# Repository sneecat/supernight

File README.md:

# Supernight
Supernight is a series of wifi LED controllers with the following features:

- High current capability (8A per-channel)
- 10 bit dimming
- 25kHz+ PWM for flicker-free film operation
- Lo-Mode 1kHz PWM for higher contrast ratio
- Physical controls
- Manual override
- ArtNet compatible (lumenair, etc.)

This is a work in progress. Currently I am going into software development, to ensure that my PCB is sound before ordering.

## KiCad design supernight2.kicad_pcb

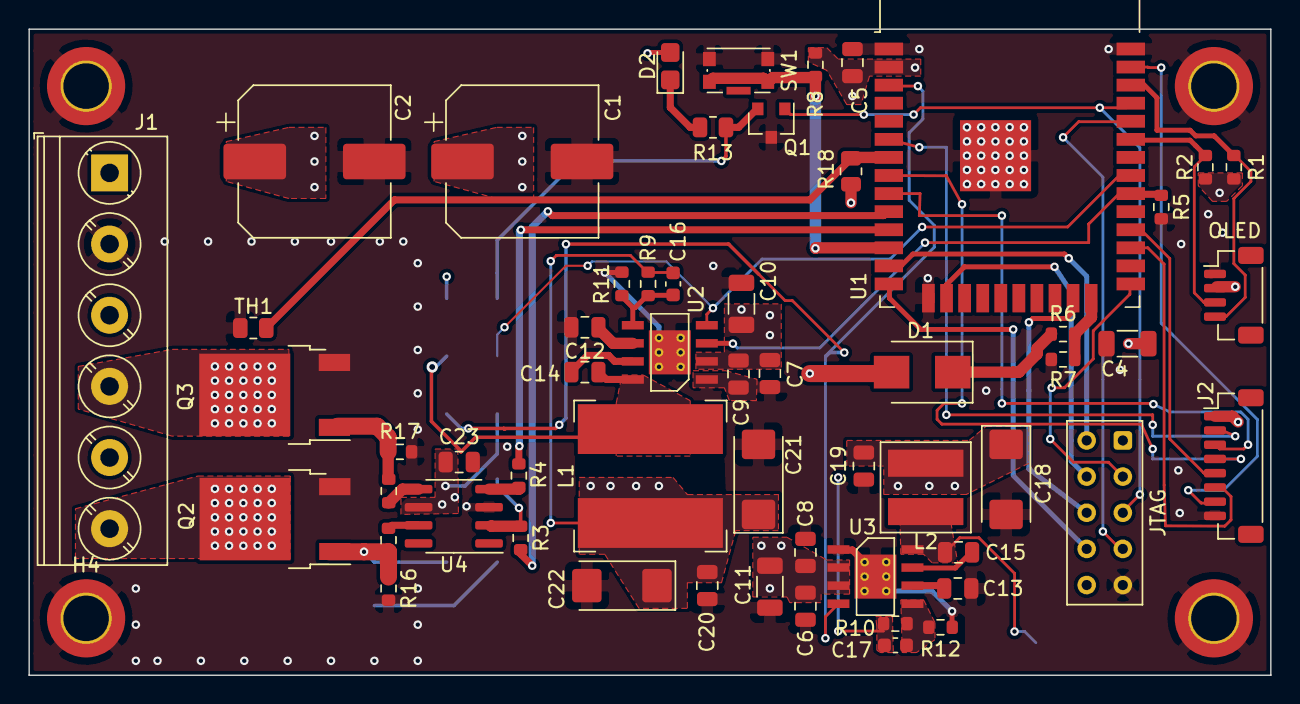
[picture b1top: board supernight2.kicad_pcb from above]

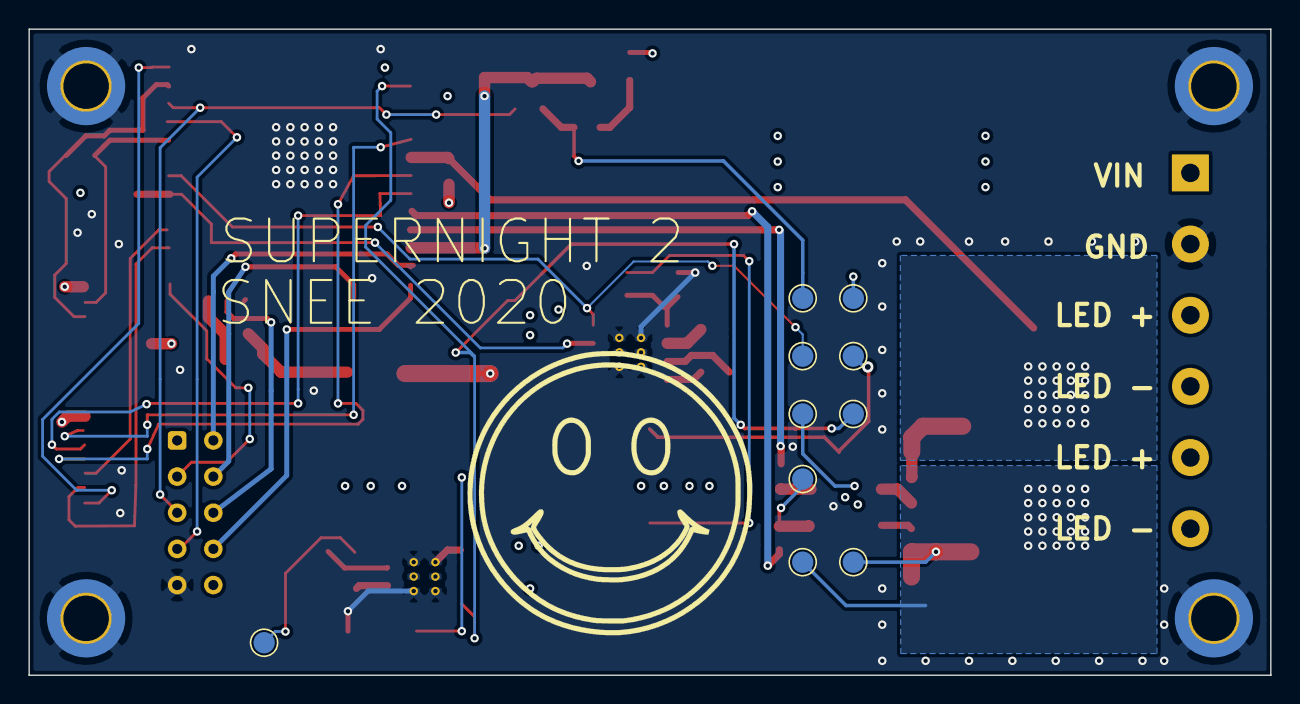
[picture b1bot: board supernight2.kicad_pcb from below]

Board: 4 copper layers, 87.2 x 45.4 mm, 72 parts (10 on the bottom side), 46 nets.

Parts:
3V3_PWGD1: 3v3_PWGD; TestPoint_Pad_D1.5mm
3V3_SW1: 3v3_SW; TestPoint_Pad_D1.5mm
12V_SW1: 12v_SW; TestPoint_Pad_D1.5mm
12v_PWGD1: 12v_PWGD; TestPoint_Pad_D1.5mm
C1, C2: 330uF; CP_Elec_10x10.5
C4, C10, C11: 10uF; C_1206_3216Metric
C5, C12, C13, C23: 1uF; C_0805_2012Metric
C6, C7, C8, C9, C14, C15, C19, C20: 100nF; C_0805_2012Metric
C16: 10pF; C_0603_1608Metric
C17: 5pF; C_0603_1608Metric
C18, C21, C22: 47uF; CP_EIA-6032-28_Kemet-C
D1: D; D_SMB
D2: LED; LED_0805_2012Metric_Castellated
ESP_TX1: TX; TestPoint_Pad_D1.5mm
H1, H2, H3, H4: MountingHole_Pad; MountingHole_3.2mm_M3_ISO14580_Pad_TopBottom
J1: Conn_01x06_Female; TerminalBlock_Phoenix_PT-1,5-6-5.0-H_1x06_P5.00mm_Horizontal
J2: Conn_02x04_Odd_Even; JST_SH_BM08B-SRSS-TB_1x08-1MP_P1.00mm_Vertical
JTAG: HTST-105-01-T-DV; Samtec_HLE-105-02-xx-DV-TE_2x05_P2.54mm_Horizontal
L1: 22uH; L_Bourns-SRN1060
L2: 8.2uH; L_Bourns_PM42S
OLED: OLED Connector; JST_SH_BM04B-SRSS-TB_1x04-1MP_P1.00mm_Vertical
Q1: BC847C; SOT-23
Q2, Q3: DMN3010LK3; TO-252-2
R1, R2: 4.7K; R_0603_1608Metric
R3, R4, R14, R15: 1K; R_0603_1608Metric
R5, R9, R10, R16, R17: 100K; R_0603_1608Metric
R6, R8: 10K; R_0603_1608Metric
R7: 1.4K; R_0603_1608Metric
R11: 9.09K; R_0603_1608Metric
R12: 43.2K; R_0603_1608Metric
R13: 33R; R_0805_2012Metric
R18: 10K; R_0805_2012Metric
Ref**: Val**; smile
SW1: SW_SPST; SW_Push_1P1T-SH_NO_CK_KMR2xxG
TH1: 10K; R_0805_2012Metric
TP1: VIN; TestPoint_Pad_D1.5mm
TP6: FET_DRV_VIN; TestPoint_Pad_D1.5mm
TP7: CH1_FET_G; TestPoint_Pad_D1.5mm
TP8: CH1_FET_D; TestPoint_Pad_D1.5mm
TP9: CH1_FET_SIG; TestPoint_Pad_D1.5mm
U1: ESP32; ESP32-WROOM-32
U2: LMR33640ADDA; PowerPad-SOIC-8
U3: LMR33610ADDA; PowerPad-SOIC-8
U4: EL7202CN; SOIC-8_3.9x4.9mm_P1.27mm

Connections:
3V3_PWGD: 3V3_PWGD1.1, U1.3, U3.4
12v_EN: R5.1, U1.30, U2.3
12v_PWGD: 12v_PWGD1.1, U1.31, U2.4
+3V3: C4.1, C5.1, C17.1, C18.1, C19.1, D2.2, J2.1, JTAG.1, L2.2, OLED.2, R1.1, R2.1, R8.1, R10.1, R18.1, U1.2
+12V: C16.1, C20.1, C21.1, C22.1, C23.2, L1.2, R9.1, TP6.1, U4.6
/CH1_SIG: R3.2, U1.10
/CH2_SIG: R4.2, U1.11
/MOSFET_DRIVE/CH1_FET_DRV: R14.2, U4.7
/MOSFET_DRIVE/CH1_FET_DRV_R: Q2.1, R14.1, R16.1, TP7.1
/MOSFET_DRIVE/CH2_FET_DRV: R15.2, U4.5
/MOSFET_DRIVE/CH2_FET_DRV_R: Q3.1, R15.1, R17.1
/MOSFET_DRIVE/LED_L_1: J1.6, Q2.2, TP8.1
/MOSFET_DRIVE/LED_L_2: J1.4, Q3.2
/Power Supply/3V3_CBOOT: C15.1, U3.7
/Power Supply/3V3_FB: C17.2, R10.2, R12.1, U3.5
/Power Supply/3V3_SW: 3V3_SW1.1, C15.2, L2.1, U3.8
/Power Supply/3v3_5V_LDO: C13.1, U3.6
/Power Supply/12V_5V_LDO: C12.1, U2.6
/Power Supply/12V_CBOOT: C14.1, U2.7
/Power Supply/12V_FB: C16.2, R9.2, R11.1, U2.5
/Power Supply/12V_SW: 12V_SW1.1, C14.2, L1.1, U2.8
/TX LED/ESP_TX_BUFF: ESP_TX1.1, Q1.2, R13.2
/VDD_SENSE: D1.1, R6.1
/VDD_SENSE_R: R6.2, R7.1, U1.24
BTN_SEL_1: J2.2, U1.6
BTN_SEL_2: J2.7, U1.37
CH1_SIG_R: R3.1, TP9.1, U4.2
CH2_SIG_R: R4.1, U4.4
ESP_BOOT_L: JTAG.3, U1.25
ESP_RX: JTAG.7, U1.34
ESP_SLP_L: R8.2, SW1.1, U1.12
ESP_TX: JTAG.5, Q1.1, U1.35
GND: C1.2, C2.2, C4.2, C5.2, C6.2, C7.2, C8.2, C9.2, C10.2, C11.2, C12.2, C13.2, C18.2, C19.2, C20.2, C21.2, C22.2, C23.1, H1.1, H2.1, H3.1, H4.1, J1.2, J2.8, JTAG.9, OLED.1, Q1.3, Q2.3, Q3.3, R5.2, R7.2, R11.2, R12.2, R16.2, R17.2, SW1.2, TH1.2, U1.1, U1.15, U1.38, U1.39, U2.1, U2.9, U3.1, U3.9, U4.3
unnamed: D2.1, R13.1
OLED_SCL: OLED.4, R1.2, U1.36
OLED_SDA: OLED.3, R2.2, U1.33
ROT1_A: J2.3, U1.9
ROT1_B: J2.4, U1.8
ROT2_A: J2.5, U1.28
ROT2_B: J2.6, U1.27
TCK: JTAG.4, U1.16
TDI: JTAG.8, U1.14
TDO: JTAG.6, U1.23
TEMP_FB: R18.2, TH1.1, U1.7
TMS: JTAG.2, U1.13
VDD: C1.1, C2.1, C6.1, C7.1, C8.1, C9.1, C10.1, C11.1, D1.2, J1.1, J1.3, J1.5, TP1.1, U2.2, U3.2, U3.3

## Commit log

2020-11-16 init
2020-11-18 added fets and driver
2020-11-18 described project
2020-11-18 Update LICENSE
2020-11-19 test opamp please ignore
2020-11-19 added better psu
2020-11-19 added sheet schematics
2020-11-19 part consolidation
2020-11-19 volt sense and encoders
2020-11-25 started pcb
2020-11-25 first layout pass finished
2020-11-27 soft release v0.2
2020-11-27 file organization
2020-11-27 file org
2020-11-27 soft release render
2020-11-27 updated to reflect release status
2020-11-27 initial code setup
2020-11-28 rearranged pcb
2020-11-28 shrunk pcb somewhat
2020-11-28 changed fets due to avail/price
2020-12-06 changed connector locations
2020-12-06 ran most of the power
2020-12-07 corrected esp32 pins and buck layout
2020-12-08 re-linked refs from brd to sch
2020-12-08 adding therm vias and silk markings
2020-12-09 added via fence and testpoints
2020-12-12 finished re-layout
2020-12-12 fixing refs, thermal pads, mosfet thermals
2020-12-12 removed git head from file
2020-12-12 final checks, adding 3d models
2020-12-12 fixed photo
2020-12-14 BOM prep
